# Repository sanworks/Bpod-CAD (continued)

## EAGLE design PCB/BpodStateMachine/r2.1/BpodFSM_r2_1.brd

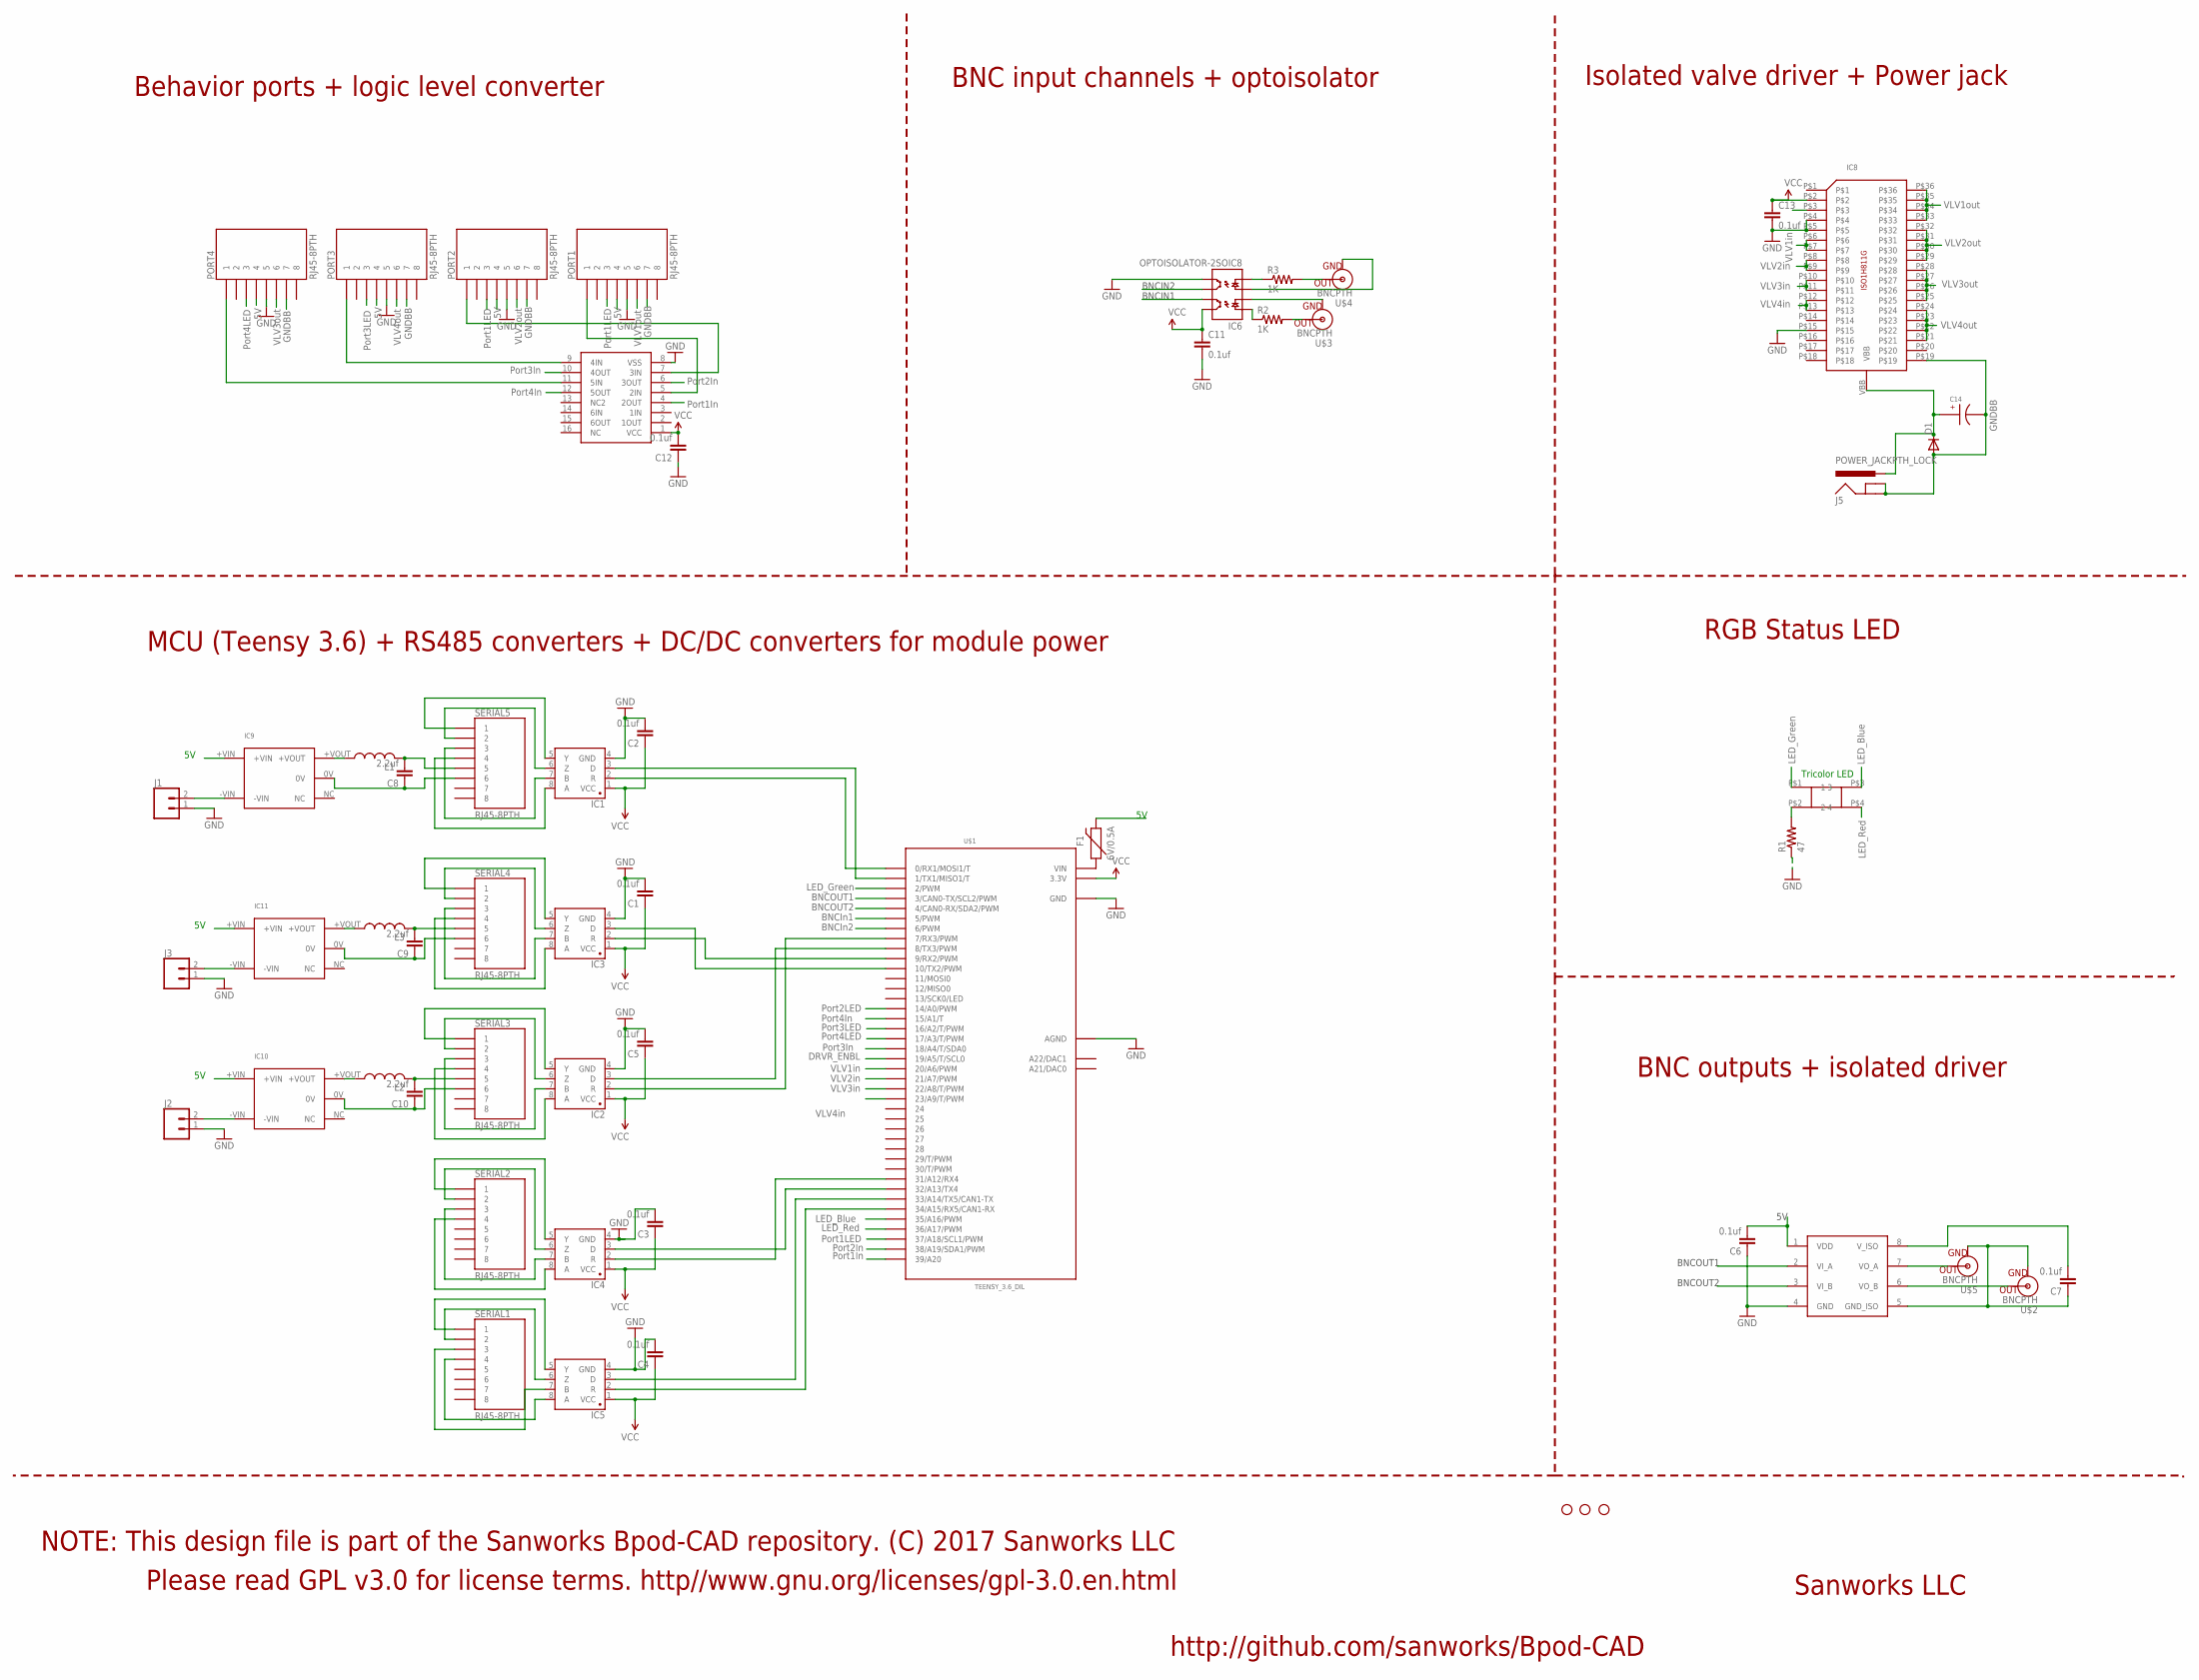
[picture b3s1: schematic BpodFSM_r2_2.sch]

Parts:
C1, C2, C3, C4, C5, C6, C7, C11, C12, C13: 0.1uf; 1206
C8, C9, C10: 2.2uf; 1206
C14: EEE-FK1H100UR
D1: DIODE-DO214AA; DO214AA
F1: 6V/0.5A; 1206
IC1, IC2, IC3, IC4, IC5: SN65HVD31DR; SO08
IC6: OPTOISOLATOR-2SOIC8; SO08-2
IC7: ADUM5240; SO08
IC8: ISO1H811G
IC9, IC10, IC11: MTU1D0505MC
IC12: CD4050; SO16
J1, J2, J3: CONN_02; 1X02
J5: POWER_JACKPTH_LOCK; POWER_JACK_PTH_LOCK
JP3, JP4, JP5: STAND-OFF
L1, L2, L3: L-USL3225M; L3225M
PORT1, PORT2, PORT3, PORT4: RJ45-8PTH; RJ45-8
R1: 47; 1206
R2, R3: 1K; 1206
SERIAL1, SERIAL2, SERIAL3, SERIAL4, SERIAL5: RJ45-8PTH; RJ45-8
U$1: TEENSY_3.6_DIL
U$2, U$3, U$4, U$5: BNCPTH; BNC
U$8: SQUARE_TRICOLOR_LED

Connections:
5V: C6.2, F1.2, IC7.1 (VDD), IC9.+VIN, IC10.+VIN, IC11.+VIN, PORT1.4, PORT2.4, PORT3.4, PORT4.4
BNCIN1: IC6.7 (EM1), U$1.6 (6/PWM)
BNCIN2: IC6.6 (CL2), U$1.5 (5/PWM)
BNCOUT1: IC7.3 (VI_B), U$1.4 (4/CAN0-RX/SDA2/PWM)
BNCOUT2: IC7.2 (VI_A), U$1.3 (3/CAN0-TX/SCL2/PWM)
DRVR_ENBL: IC8.P$3, U$1.19/A5 (19/A5/T/SCL0)
GND: C1.2, C2.2, C3.2, C4.2, C5.2, C6.1, C11.2, C12.1, C13.2, IC1.4 (GND), IC2.4 (GND), IC3.4 (GND), IC4.4 (GND), IC5.4 (GND), IC6.5 (EM2), IC7.4 (GND), IC8.P$4, IC8.P$5, IC8.P$15, IC12.8 (VSS), J1.1, J2.1, J3.1, PORT1.5, PORT2.5, PORT3.5, PORT4.5, R1.1, U$1.AGND, U$1.GND, U$1.GND1 (GND)
GNDBB: C14.CATHODE, D1.A, IC8.P$19, J5.GND, J5.GNDBREAK, PORT1.7, PORT2.7, PORT3.7, PORT4.7; also elsewhere on the board
ISOGND: C7.1, IC7.5 (GND_ISO), U$2.GND, U$5.GND
LED_BLUE: U$1.35/A16 (35/A16/PWM), U$8.P$3 (3)
LED_GREEN: U$1.2 (2/PWM), U$8.P$1 (1)
LED_RED: U$1.36/A17 (36/A17/PWM), U$8.P$4 (4)
unnamed: IC3.8 (A), SERIAL4.4
unnamed: IC3.7 (B), SERIAL4.3
unnamed: IC3.6 (Z), SERIAL4.2
unnamed: IC3.5 (Y), SERIAL4.1
unnamed: IC3.2 (R), U$1.9 (9/RX2/PWM)
unnamed: IC3.3 (D), U$1.10 (10/TX2/PWM)
unnamed: IC1.8 (A), SERIAL5.4
unnamed: IC1.7 (B), SERIAL5.3
unnamed: IC1.6 (Z), SERIAL5.2
unnamed: IC1.5 (Y), SERIAL5.1
unnamed: IC1.2 (R), U$1.0 (0/RX1/MOSI1/T)
unnamed: IC1.3 (D), U$1.1 (1/TX1/MISO1/T)
unnamed: IC6.3 (A2), U$4.GND
unnamed: R3.2, U$4.S (OUT)
unnamed: R2.2, U$3.S (OUT)
unnamed: IC6.2 (C1), U$3.GND
unnamed: IC2.8 (A), SERIAL3.4
unnamed: IC2.7 (B), SERIAL3.3
unnamed: IC2.6 (Z), SERIAL3.2
unnamed: IC12.7 (3IN), PORT2.1
unnamed: IC2.5 (Y), SERIAL3.1
unnamed: IC2.2 (R), U$1.7 (7/RX3/PWM)
unnamed: C8.2, L1.2, SERIAL5.5
unnamed: IC12.9 (4IN), PORT3.1
unnamed: R1.2, U$8.P$2 (2)
unnamed: C8.1, IC9.0V, SERIAL5.6
unnamed: IC7.7 (VO_A), U$5.S (OUT)
unnamed: IC2.3 (D), U$1.8 (8/TX3/PWM)
unnamed: F1.1, U$1.VIN
unnamed: IC7.6 (VO_B), U$2.S (OUT)
unnamed: IC12.11 (5IN), PORT4.1
unnamed: IC5.8 (A), SERIAL1.4
unnamed: IC5.7 (B), SERIAL1.3
unnamed: IC5.6 (Z), SERIAL1.2
unnamed: IC5.5 (Y), SERIAL1.1
unnamed: IC4.8 (A), SERIAL2.4
unnamed: IC4.7 (B), SERIAL2.3
unnamed: IC4.6 (Z), SERIAL2.2
unnamed: IC9.+VOUT, L1.1
unnamed: IC4.5 (Y), SERIAL2.1
unnamed: IC9.-VIN, J1.2
unnamed: IC5.2 (R), U$1.34/A15 (34/A15/RX5/CAN1-RX)
unnamed: C10.1, IC10.0V, SERIAL3.6
unnamed: C10.2, L2.2, SERIAL3.5
unnamed: IC10.+VOUT, L2.1
unnamed: IC10.-VIN, J2.2
unnamed: C9.1, IC11.0V, SERIAL4.6
unnamed: IC5.3 (D), U$1.33/A14 (33/A14/TX5/CAN1-TX)
unnamed: C9.2, L3.2, SERIAL4.5
unnamed: IC11.+VOUT, L3.1
unnamed: IC11.-VIN, J3.2
unnamed: IC4.2 (R), U$1.31/A12 (31/A12/RX4)
unnamed: IC4.3 (D), U$1.32/A13 (32/A13/TX4)
unnamed: IC6.1 (A1), R2.1
unnamed: IC6.4 (C2), R3.1
unnamed: IC12.5 (2IN), PORT1.1
unnamed: C7.2, IC7.8 (V_ISO)
PORT1IN: IC12.4 (2OUT), U$1.39/A20
PORT1LED: PORT1.3, U$1.37/A18 (37/A18/SCL1/PWM)
PORT2IN: IC12.6 (3OUT), U$1.38/A19 (38/A19/SDA1/PWM)
PORT2LED: PORT2.3, U$1.14/A0 (14/A0/PWM)
PORT3IN: IC12.10 (4OUT), U$1.18/A4 (18/A4/T/SDA0)
PORT3LED: PORT3.3, U$1.16/A2 (16/A2/T/PWM)
PORT4IN: IC12.12 (5OUT), U$1.15/A1 (15/A1/T)
PORT4LED: PORT4.3, U$1.17/A3 (17/A3/T/PWM)
VBB: C14.ANODE, D1.C, IC8.VBB, J5.PWR; also elsewhere on the board
VCC: C1.1, C2.1, C3.1, C4.1, C5.1, C11.1, C12.2, C13.1, IC1.1 (VCC), IC2.1 (VCC), IC3.1 (VCC), IC4.1 (VCC), IC5.1 (VCC), IC6.8 (CL1), IC8.P$2, IC12.1 (VCC), U$1.3.3V, U$1.3.3V3 (3.3V)
VLV1IN: IC8.P$6, IC8.P$7, U$1.23/A9 (23/A9/T/PWM)
VLV1OUT: IC8.P$33, IC8.P$34, IC8.P$35, IC8.P$36, PORT1.6
VLV2IN: IC8.P$8, IC8.P$9, U$1.22/A8 (22/A8/T/PWM)
VLV2OUT: IC8.P$29, IC8.P$30, IC8.P$31, IC8.P$32, PORT2.6
VLV3IN: IC8.P$12, IC8.P$13, U$1.20/A6 (20/A6/PWM)
VLV3OUT: IC8.P$21, IC8.P$22, IC8.P$23, IC8.P$24, PORT3.6
VLV4IN: IC8.P$10, IC8.P$11, U$1.21/A7 (21/A7/PWM)
VLV4OUT: IC8.P$25, IC8.P$26, IC8.P$27, IC8.P$28, PORT4.6

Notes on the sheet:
Tricolor LED
LED_Blue
LED_Red
LED_Green
BNCIN1
BNCIN2
BNCIn1
BNCIn2
BNCOUT2
BNCOUT1
Port1In
Port2In
Port3In
Port4In
Port1LED
Port2LED
Port3LED
Port4LED
DRVR_ENBL
VLV2in
VLV3in
VLV4in
VLV1in
GNDBB
VLV1out
VLV2out
VLV3out
VLV4out
Sanworks LLC
http://github.com/sanworks/Bpod-CAD
Please read GPL v3.0 for license terms. http//www.gnu.org/licenses/gpl-3.0.en.html
NOTE: This design file is part of the Sanworks Bpod-CAD repository. (C) 2017 Sanworks LLC
Behavior ports + logic level converter
BNC input channels + optoisolator
Isolated valve driver + Power jack
RGB Status LED
BNC outputs + isolated driver
MCU (Teensy 3.6) + RS485 converters + DC/DC converters for module power

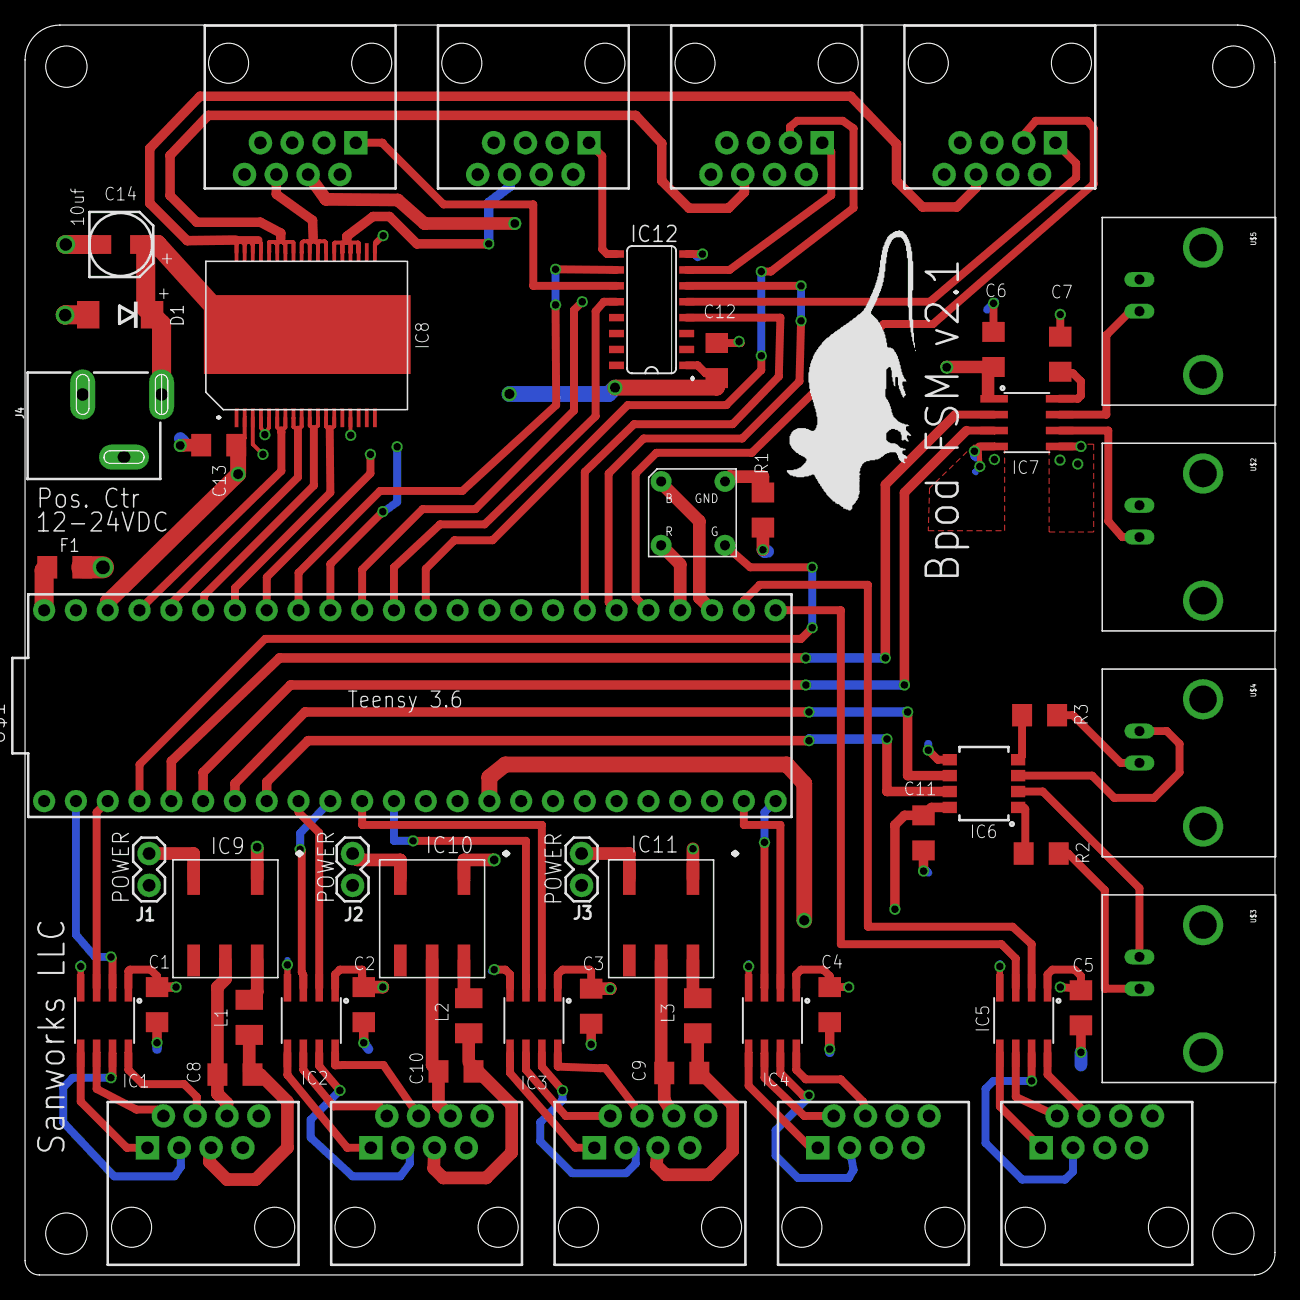
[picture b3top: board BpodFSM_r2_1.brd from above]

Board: 4 copper layers, 99.8 x 99.8 mm, 58 parts (0 on the bottom side), 87 nets.

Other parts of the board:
J4: POWER_JACKSLT; POWER_JACK_SLOT
JP1: STAND-OFF
U$9: MOUSELOGO

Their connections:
GNDBB: J4.GND@1, J4.GND@2; also elsewhere on the board
VBB: J4.PWR; also elsewhere on the board
